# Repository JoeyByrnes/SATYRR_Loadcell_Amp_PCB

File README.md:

# SATYRR Loadcell Amplifier PCB
Loadcell Amplifiers for RoboDesign Lab SATYRR Wheeled-Humanoid robot

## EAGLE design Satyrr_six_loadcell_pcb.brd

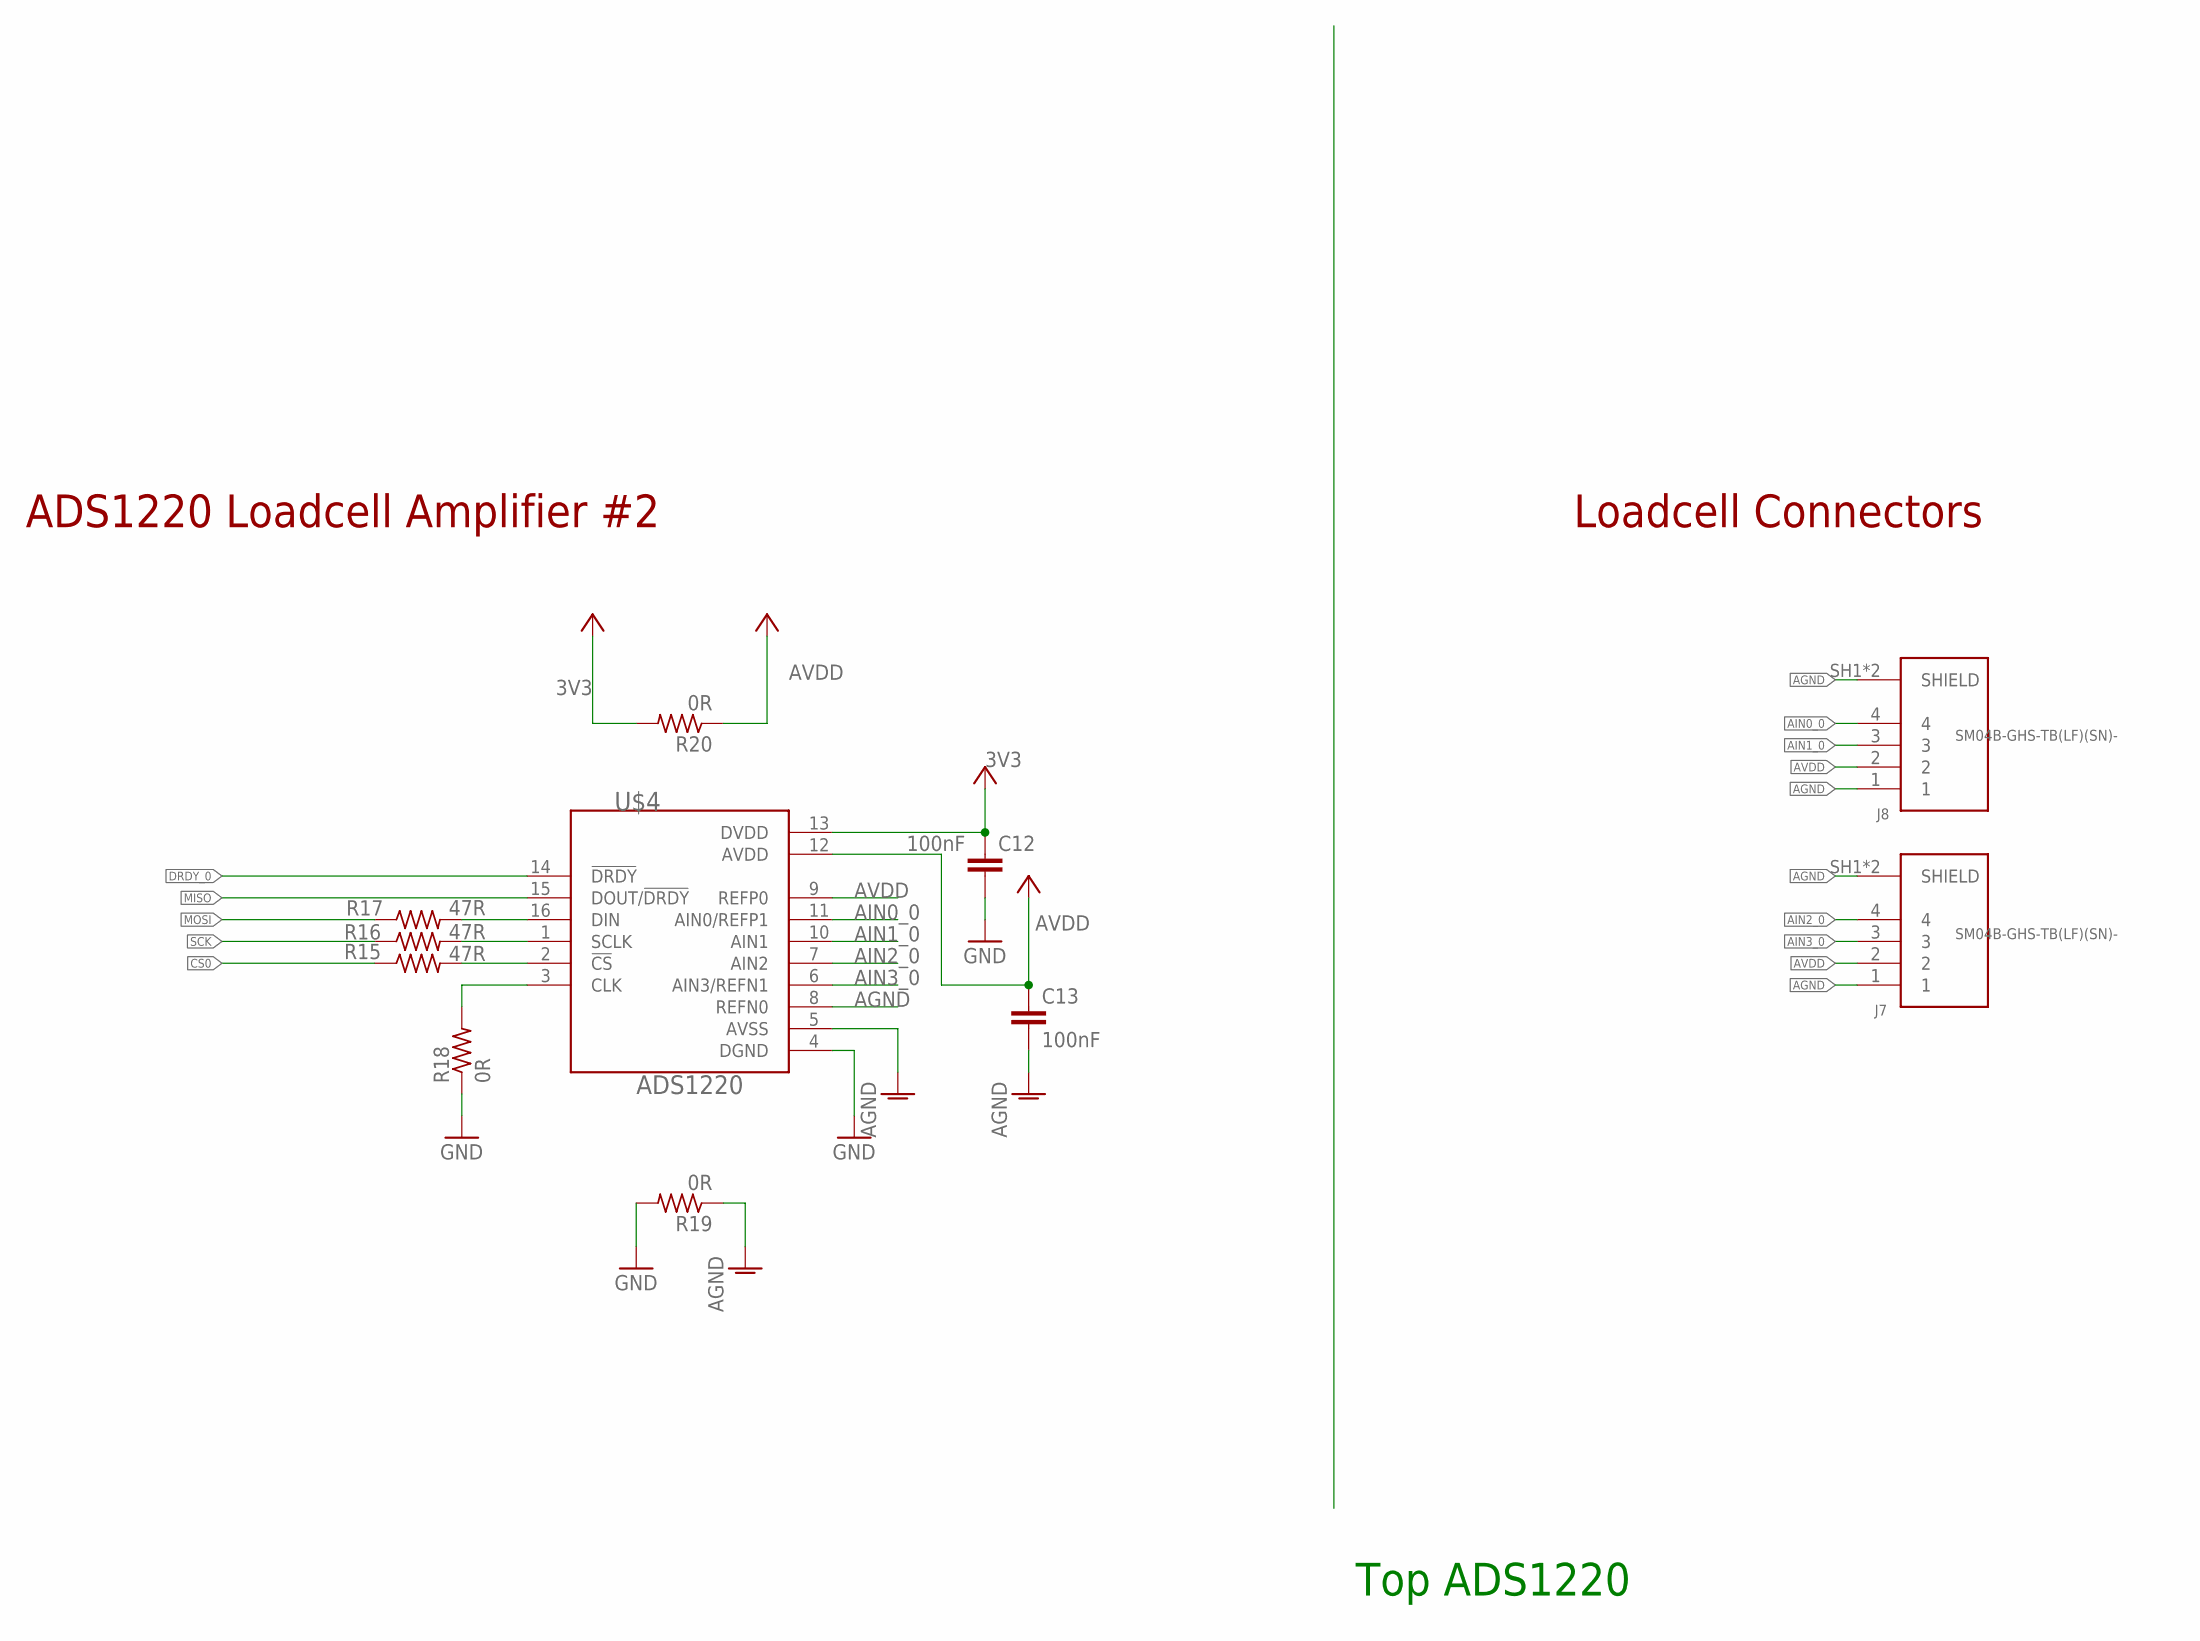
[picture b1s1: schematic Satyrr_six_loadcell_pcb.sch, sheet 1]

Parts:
C12, C13: 100nF; C0603
J7, J8: SM04B-GHS-TB(LF)(SN)-; JST_SM04B-GHS-TB(LF)(SN)-
R15, R16, R17: 47R; R0603
R18, R19, R20: 0R; R0603
U$4: ADS1220; TSSOP-16

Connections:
3V3: C12.1, R20.2, U$4.13 (DVDD); also elsewhere on the board
AGND: C13.2, J7.1, J7.SH1 (SHIELD), J7.SH2 (SHIELD), J8.1, J8.SH1 (SHIELD), J8.SH2 (SHIELD), R19.1, U$4.5 (AVSS), U$4.8 (REFN0); also elsewhere on the board
AIN0_0: J8.4, U$4.11 (AIN0/REFP1)
AIN1_0: J8.3, U$4.10 (AIN1)
AIN2_0: J7.4, U$4.7 (AIN2)
AIN3_0: J7.3, U$4.6 (AIN3/REFN1)
AVDD: C13.1, J7.2, J8.2, R20.1, U$4.9 (REFP0), U$4.12 (AVDD); also elsewhere on the board
CS0: R15.1; also elsewhere on the board
DRDY_0: U$4.14 (!DRDY); also elsewhere on the board
GND: C12.2, R18.1, R19.2, U$4.4 (DGND); also elsewhere on the board
MISO: U$4.15 (DOUT/!DRDY); also elsewhere on the board
MOSI: R17.1; also elsewhere on the board
unnamed: R17.2, U$4.16 (DIN)
unnamed: R16.2, U$4.1 (SCLK)
unnamed: R15.2, U$4.2 (!CS)
unnamed: R18.2, U$4.3 (CLK)
SCK: R16.1; also elsewhere on the board

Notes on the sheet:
Top ADS1220
ADS1220 Loadcell Amplifier #2
Loadcell Connectors

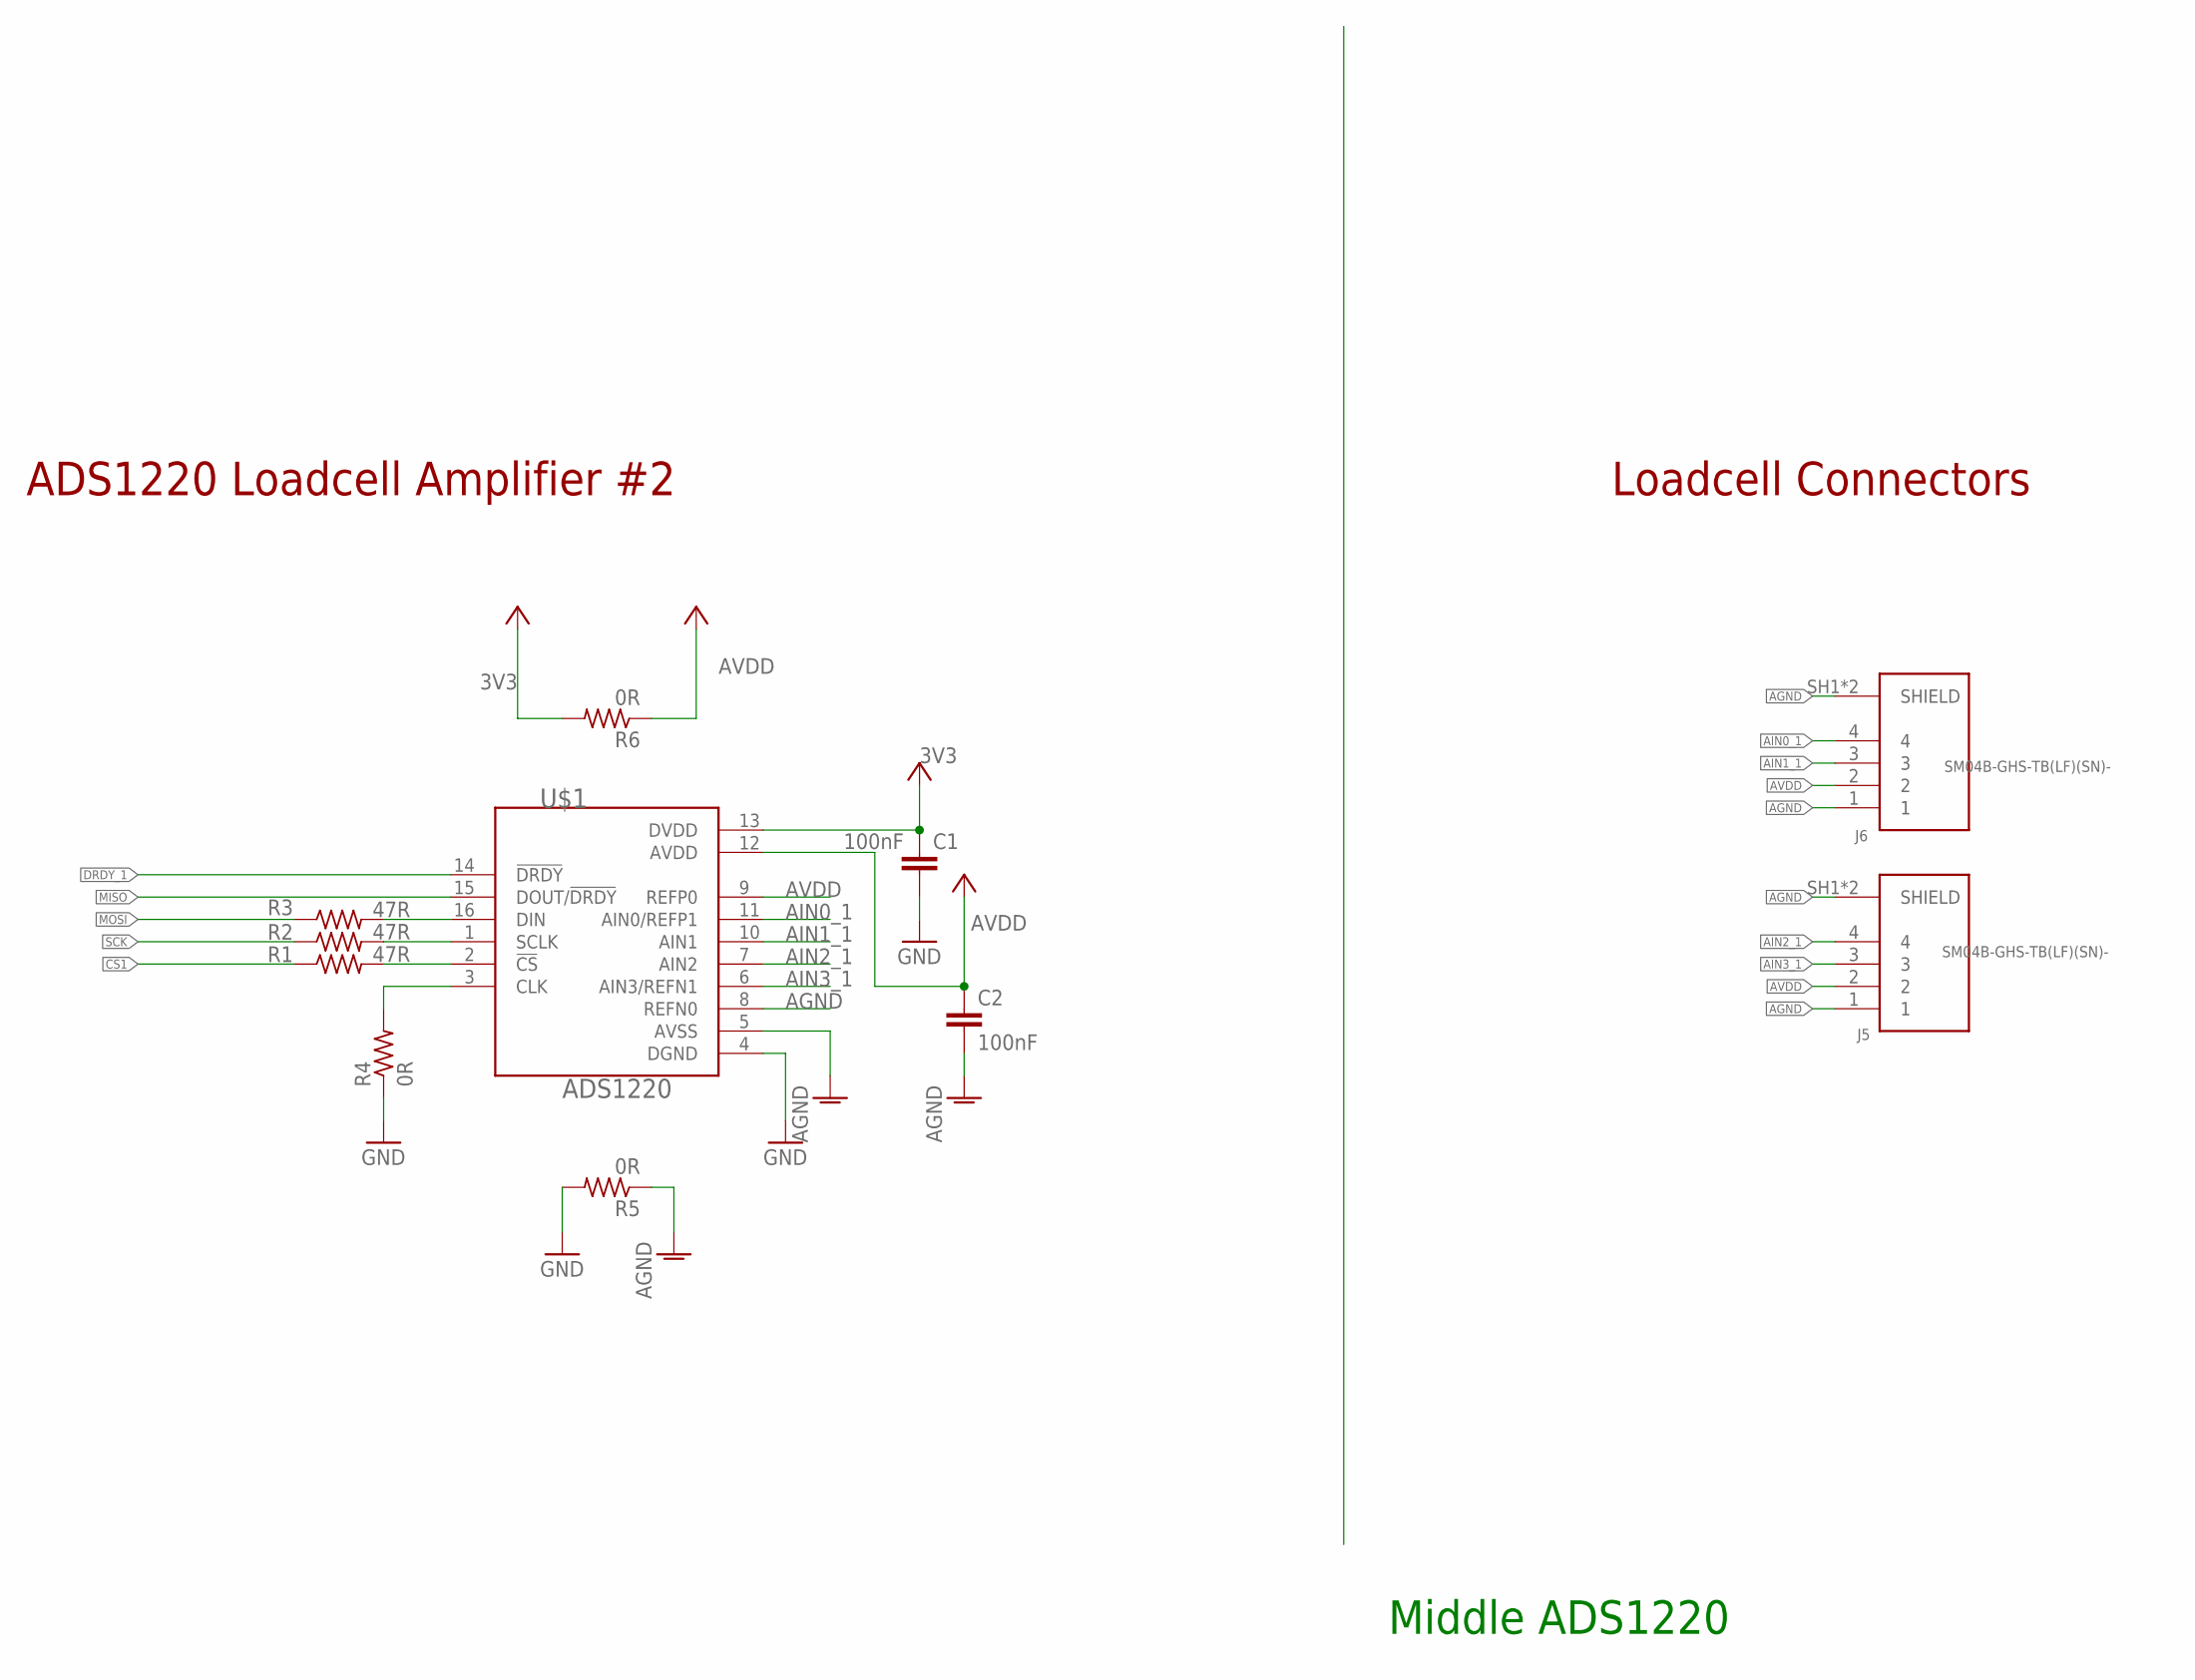
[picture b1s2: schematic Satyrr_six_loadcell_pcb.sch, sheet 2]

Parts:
C1, C2: 100nF; C0603
J5, J6: SM04B-GHS-TB(LF)(SN)-; JST_SM04B-GHS-TB(LF)(SN)-
R1, R2, R3: 47R; R0603
R4, R5, R6: 0R; R0603
U$1: ADS1220; TSSOP-16

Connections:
3V3: C1.1, R6.2, U$1.13 (DVDD); also elsewhere on the board
AGND: C2.2, J5.1, J5.SH1 (SHIELD), J5.SH2 (SHIELD), J6.1, J6.SH1 (SHIELD), J6.SH2 (SHIELD), R5.1, U$1.5 (AVSS), U$1.8 (REFN0); also elsewhere on the board
AIN0_1: J6.4, U$1.11 (AIN0/REFP1)
AIN1_1: J6.3, U$1.10 (AIN1)
AIN2_1: J5.4, U$1.7 (AIN2)
AIN3_1: J5.3, U$1.6 (AIN3/REFN1)
AVDD: C2.1, J5.2, J6.2, R6.1, U$1.9 (REFP0), U$1.12 (AVDD); also elsewhere on the board
CS1: R1.1; also elsewhere on the board
DRDY_1: U$1.14 (!DRDY); also elsewhere on the board
GND: C1.2, R4.1, R5.2, U$1.4 (DGND); also elsewhere on the board
MISO: U$1.15 (DOUT/!DRDY); also elsewhere on the board
MOSI: R3.1; also elsewhere on the board
unnamed: R3.2, U$1.16 (DIN)
unnamed: R2.2, U$1.1 (SCLK)
unnamed: R1.2, U$1.2 (!CS)
unnamed: R4.2, U$1.3 (CLK)
SCK: R2.1; also elsewhere on the board

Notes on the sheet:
Middle ADS1220
ADS1220 Loadcell Amplifier #2
Loadcell Connectors

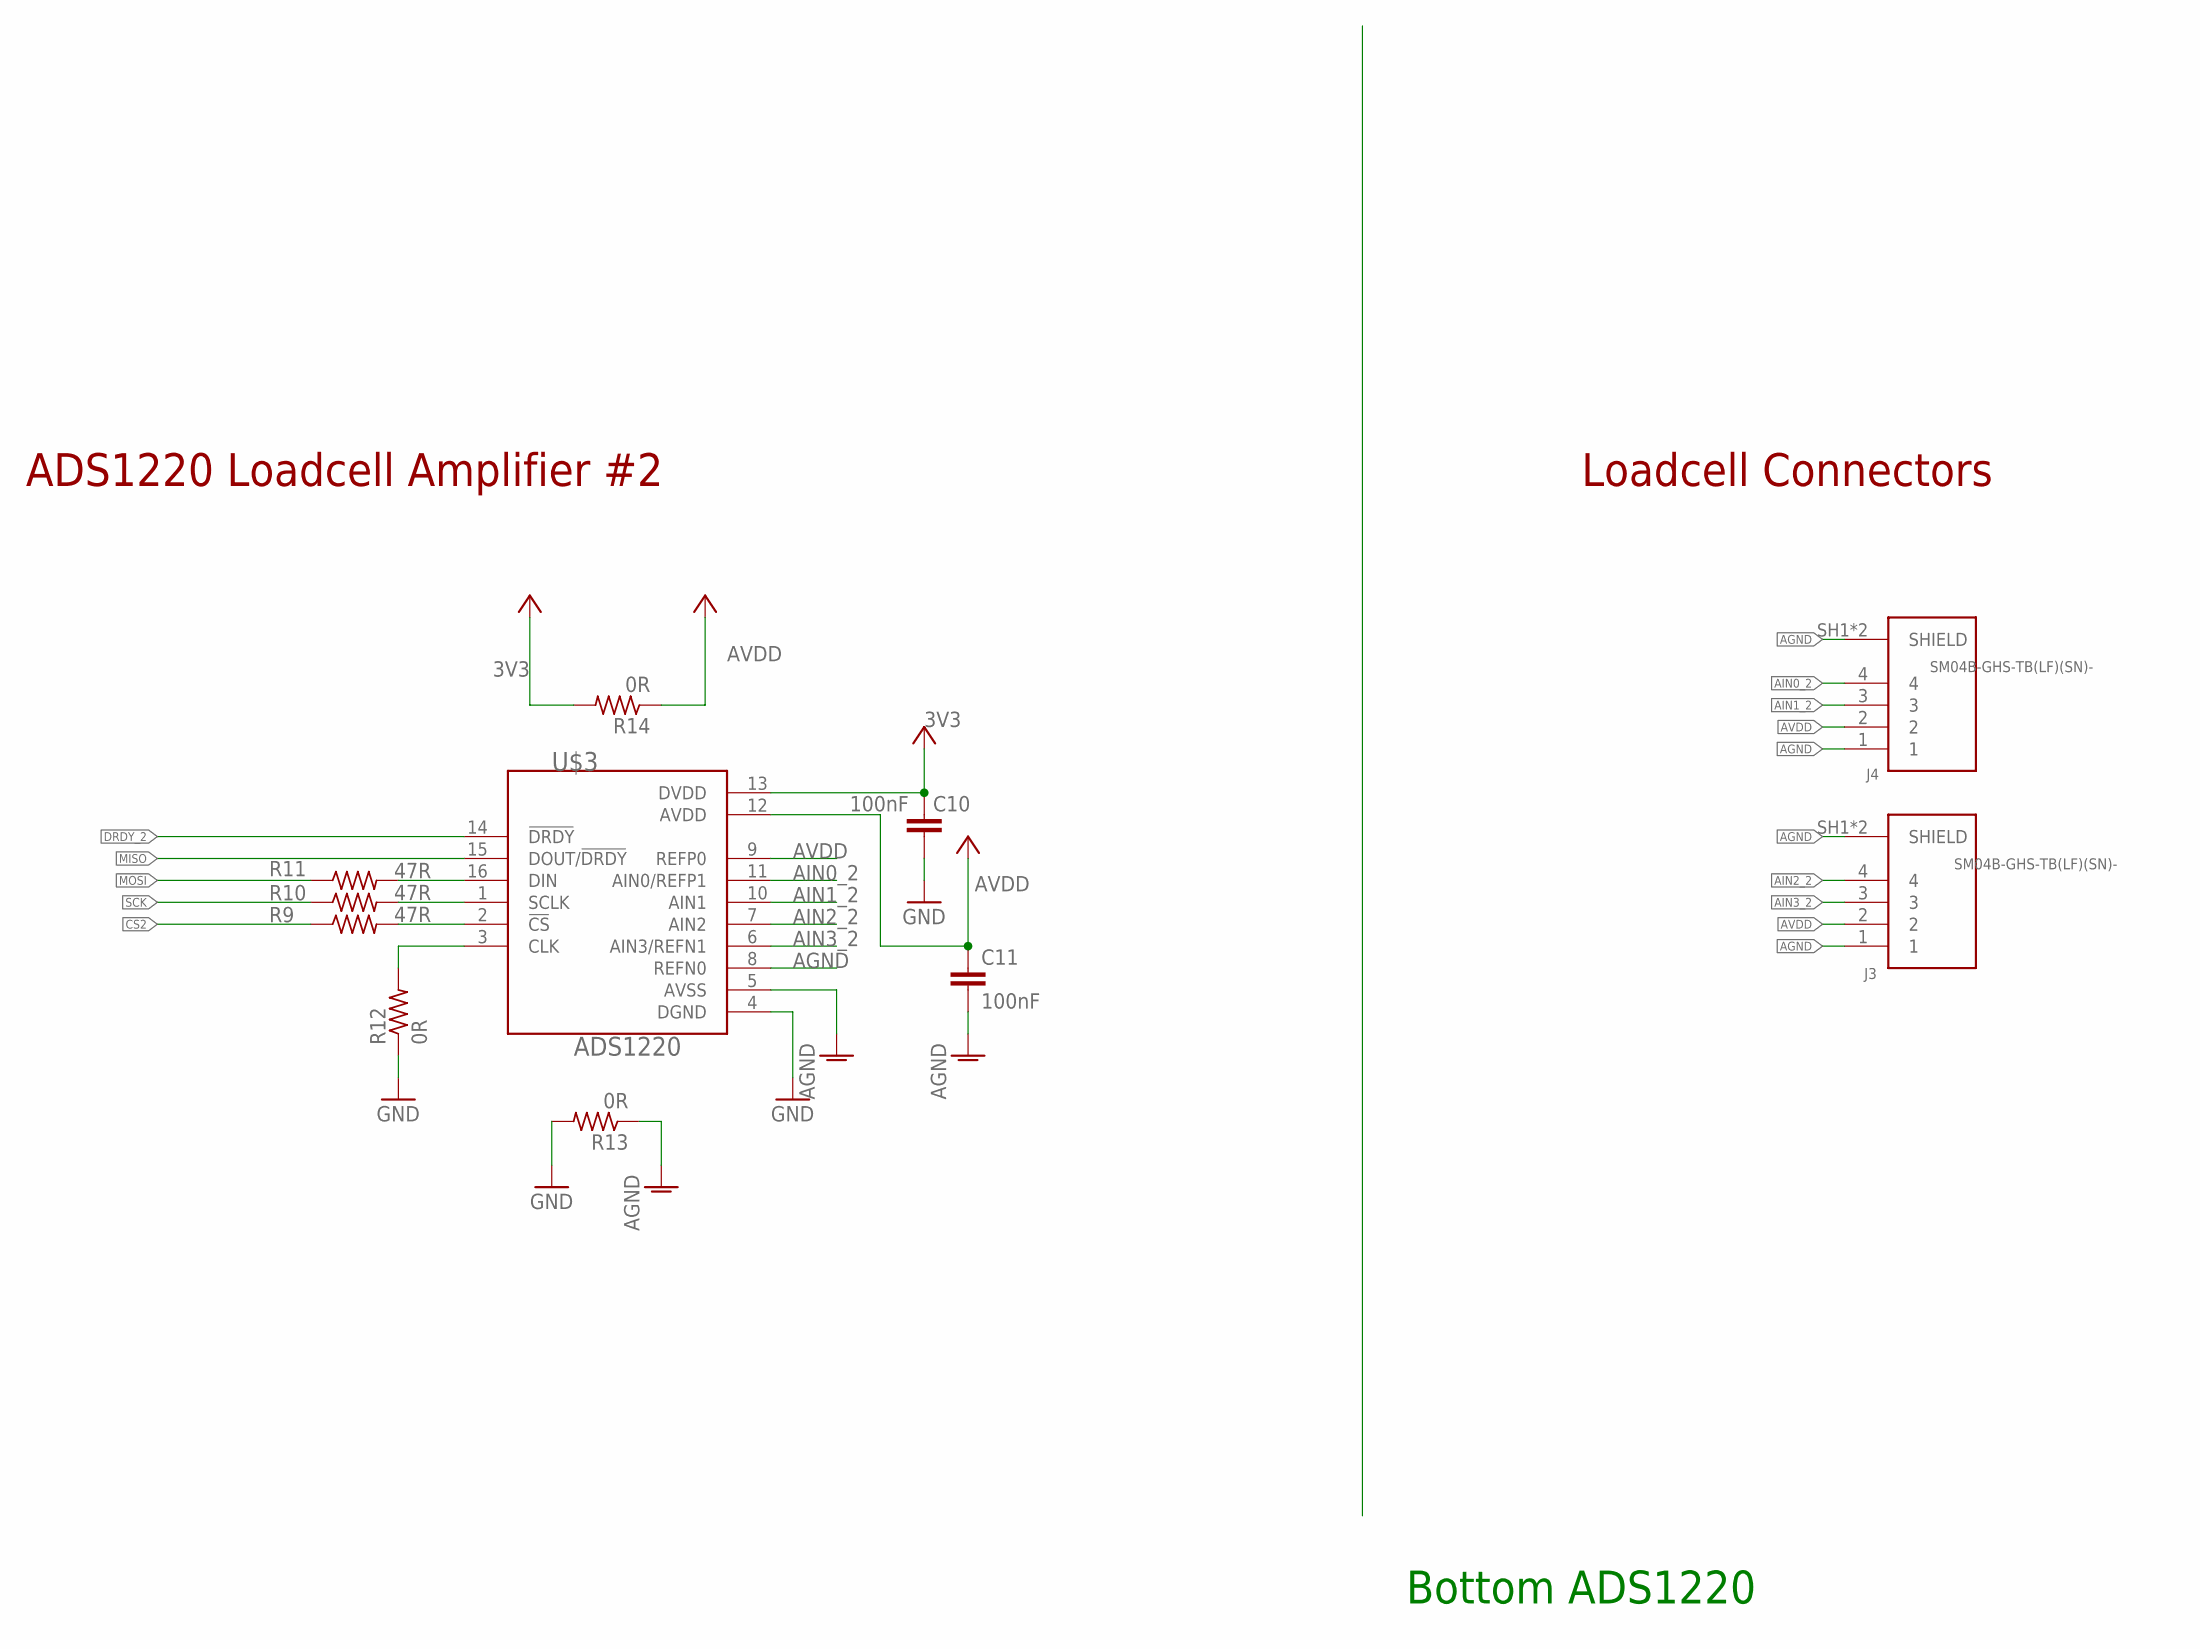
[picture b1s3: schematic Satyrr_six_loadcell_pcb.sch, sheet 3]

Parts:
C10, C11: 100nF; C0603
J3, J4: SM04B-GHS-TB(LF)(SN)-; JST_SM04B-GHS-TB(LF)(SN)-
R9, R10, R11: 47R; R0603
R12, R13, R14: 0R; R0603
U$3: ADS1220; TSSOP-16

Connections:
3V3: C10.1, R14.2, U$3.13 (DVDD); also elsewhere on the board
AGND: C11.2, J3.1, J3.SH1 (SHIELD), J3.SH2 (SHIELD), J4.1, J4.SH1 (SHIELD), J4.SH2 (SHIELD), R13.1, U$3.5 (AVSS), U$3.8 (REFN0); also elsewhere on the board
AIN0_2: J4.4, U$3.11 (AIN0/REFP1)
AIN1_2: J4.3, U$3.10 (AIN1)
AIN2_2: J3.4, U$3.7 (AIN2)
AIN3_2: J3.3, U$3.6 (AIN3/REFN1)
AVDD: C11.1, J3.2, J4.2, R14.1, U$3.9 (REFP0), U$3.12 (AVDD); also elsewhere on the board
CS2: R9.1; also elsewhere on the board
DRDY_2: U$3.14 (!DRDY); also elsewhere on the board
GND: C10.2, R12.1, R13.2, U$3.4 (DGND); also elsewhere on the board
MISO: U$3.15 (DOUT/!DRDY); also elsewhere on the board
MOSI: R11.1; also elsewhere on the board
unnamed: R11.2, U$3.16 (DIN)
unnamed: R10.2, U$3.1 (SCLK)
unnamed: R9.2, U$3.2 (!CS)
unnamed: R12.2, U$3.3 (CLK)
SCK: R10.1; also elsewhere on the board

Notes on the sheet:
Bottom ADS1220
ADS1220 Loadcell Amplifier #2
Loadcell Connectors

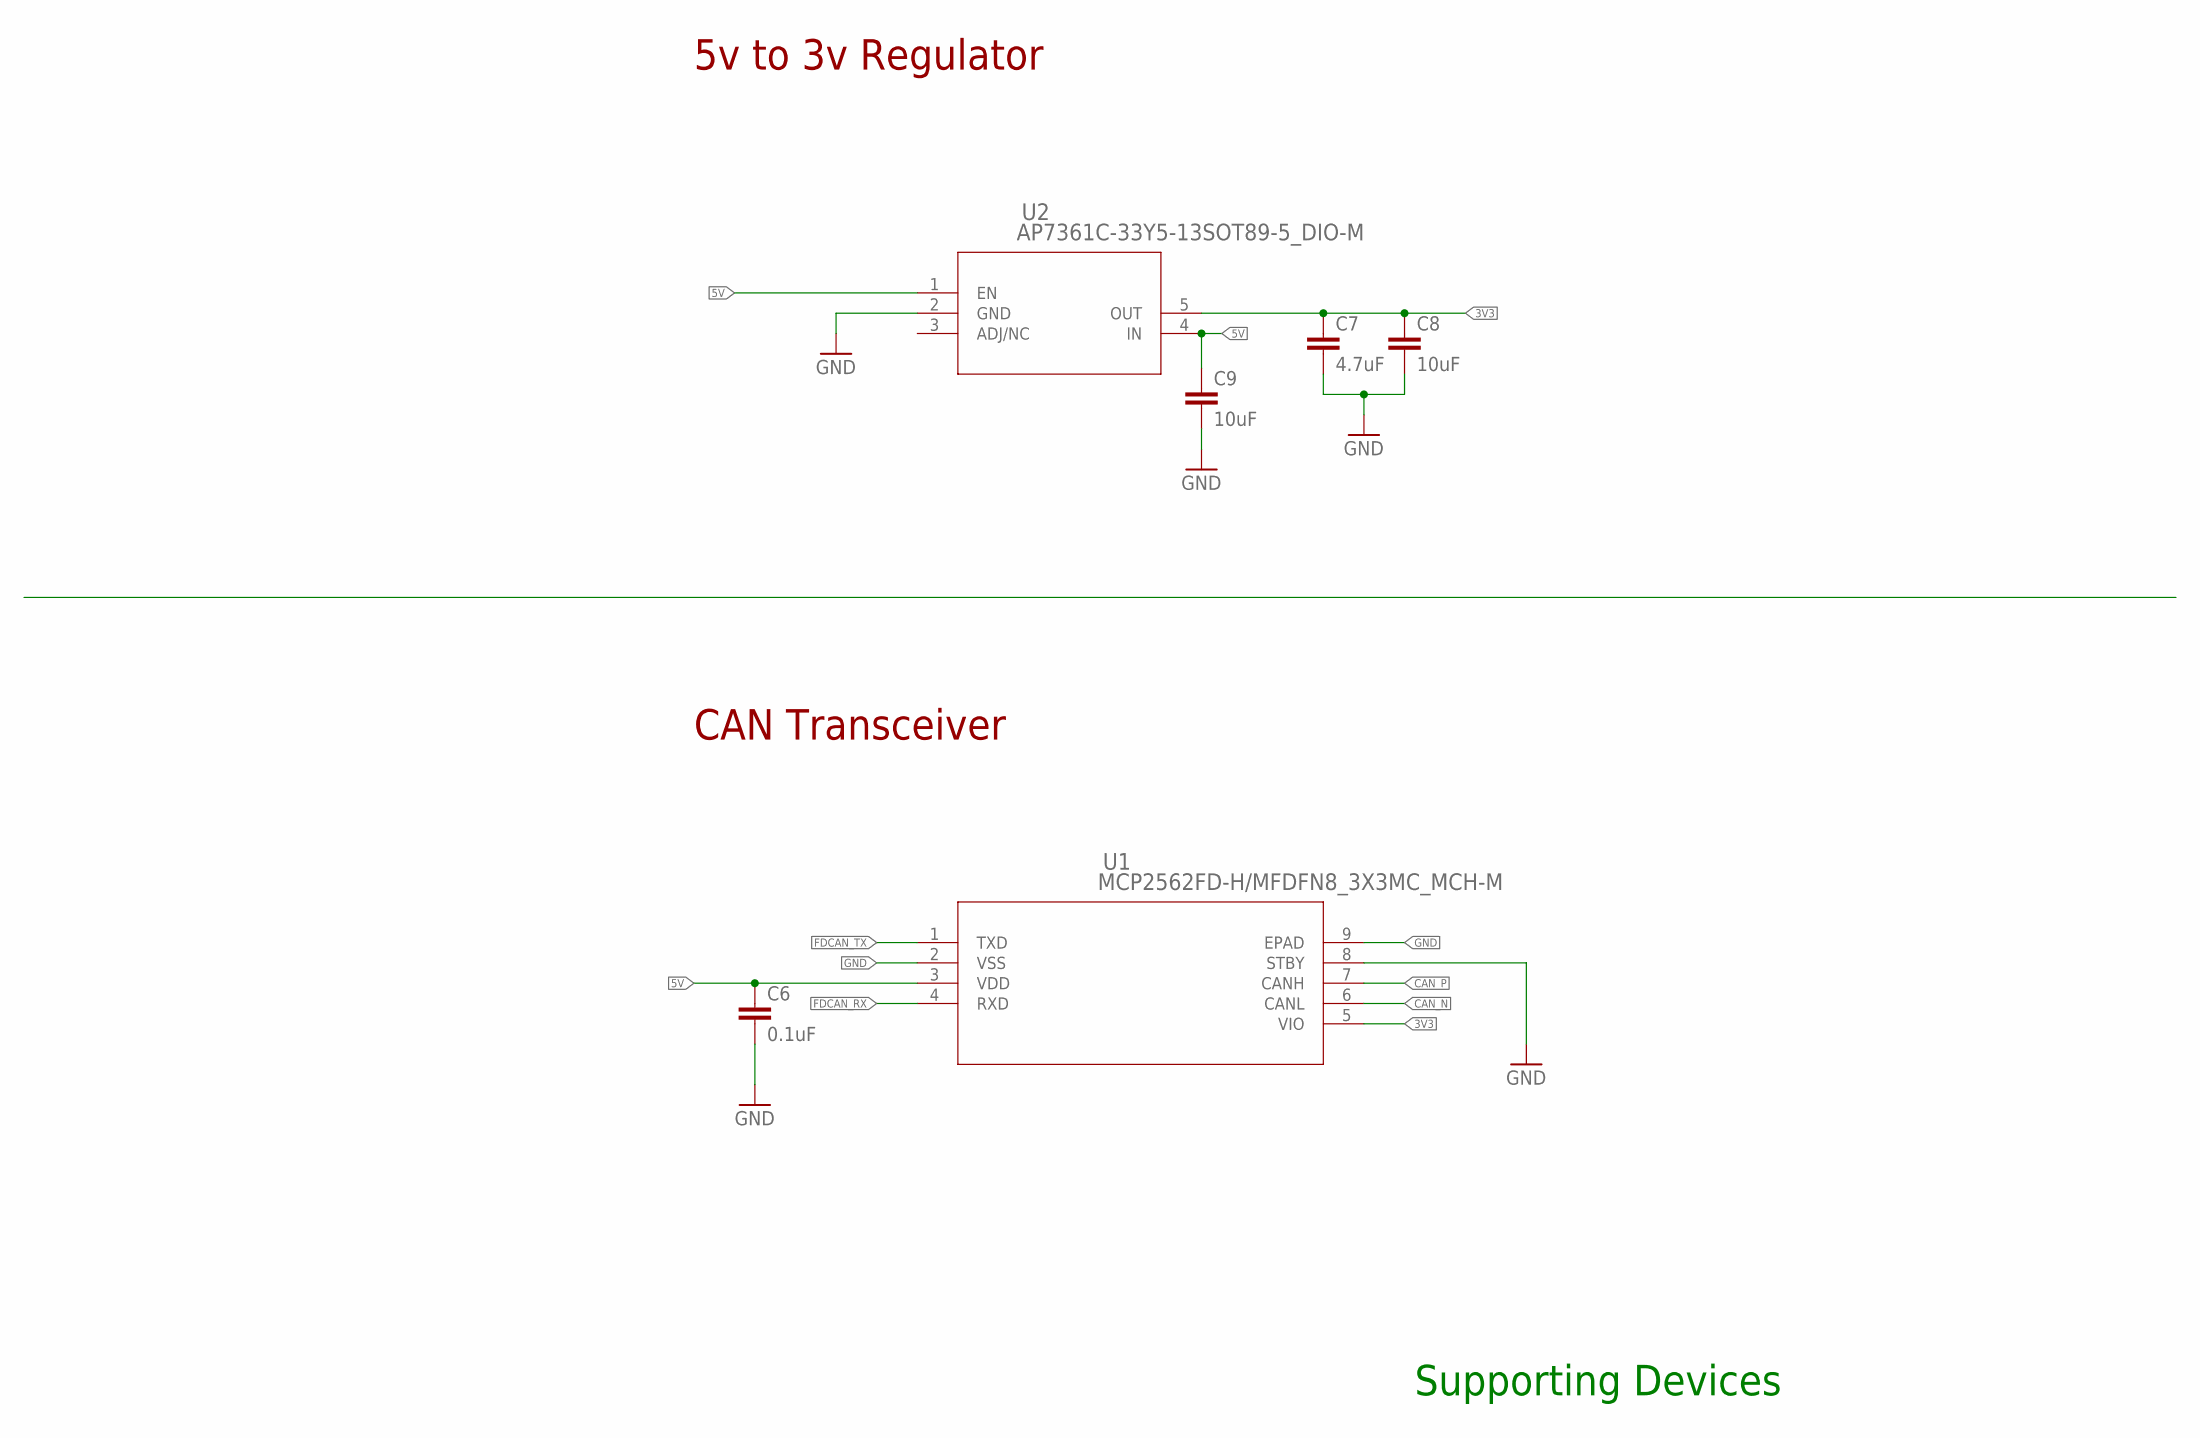
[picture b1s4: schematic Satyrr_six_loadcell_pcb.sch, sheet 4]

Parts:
C6: 0.1uF; C0603
C7: 4.7uF; C0603
C8, C9: 10uF; C0603
U1: MCP2562FD-H/MFDFN8_3X3MC_MCH-M; DFN8_3X3MC_MCH-M
U2: AP7361C-33Y5-13SOT89-5_DIO-M; SOT89-5_DIO-M

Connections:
3V3: C7.1, C8.1, U1.5 (VIO), U2.5 (OUT); also elsewhere on the board
5V: C6.1, C9.1, U1.3 (VDD), U2.1 (EN), U2.4 (IN); also elsewhere on the board
CAN_N: U1.6 (CANL); also elsewhere on the board
CAN_P: U1.7 (CANH); also elsewhere on the board
FDCAN_RX: U1.4 (RXD); also elsewhere on the board
FDCAN_TX: U1.1 (TXD); also elsewhere on the board
GND: C6.2, C7.2, C8.2, C9.2, U1.2 (VSS), U1.8 (STBY), U1.9 (EPAD), U2.2 (GND); also elsewhere on the board

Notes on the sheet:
5v to 3v Regulator
CAN Transceiver
Supporting Devices

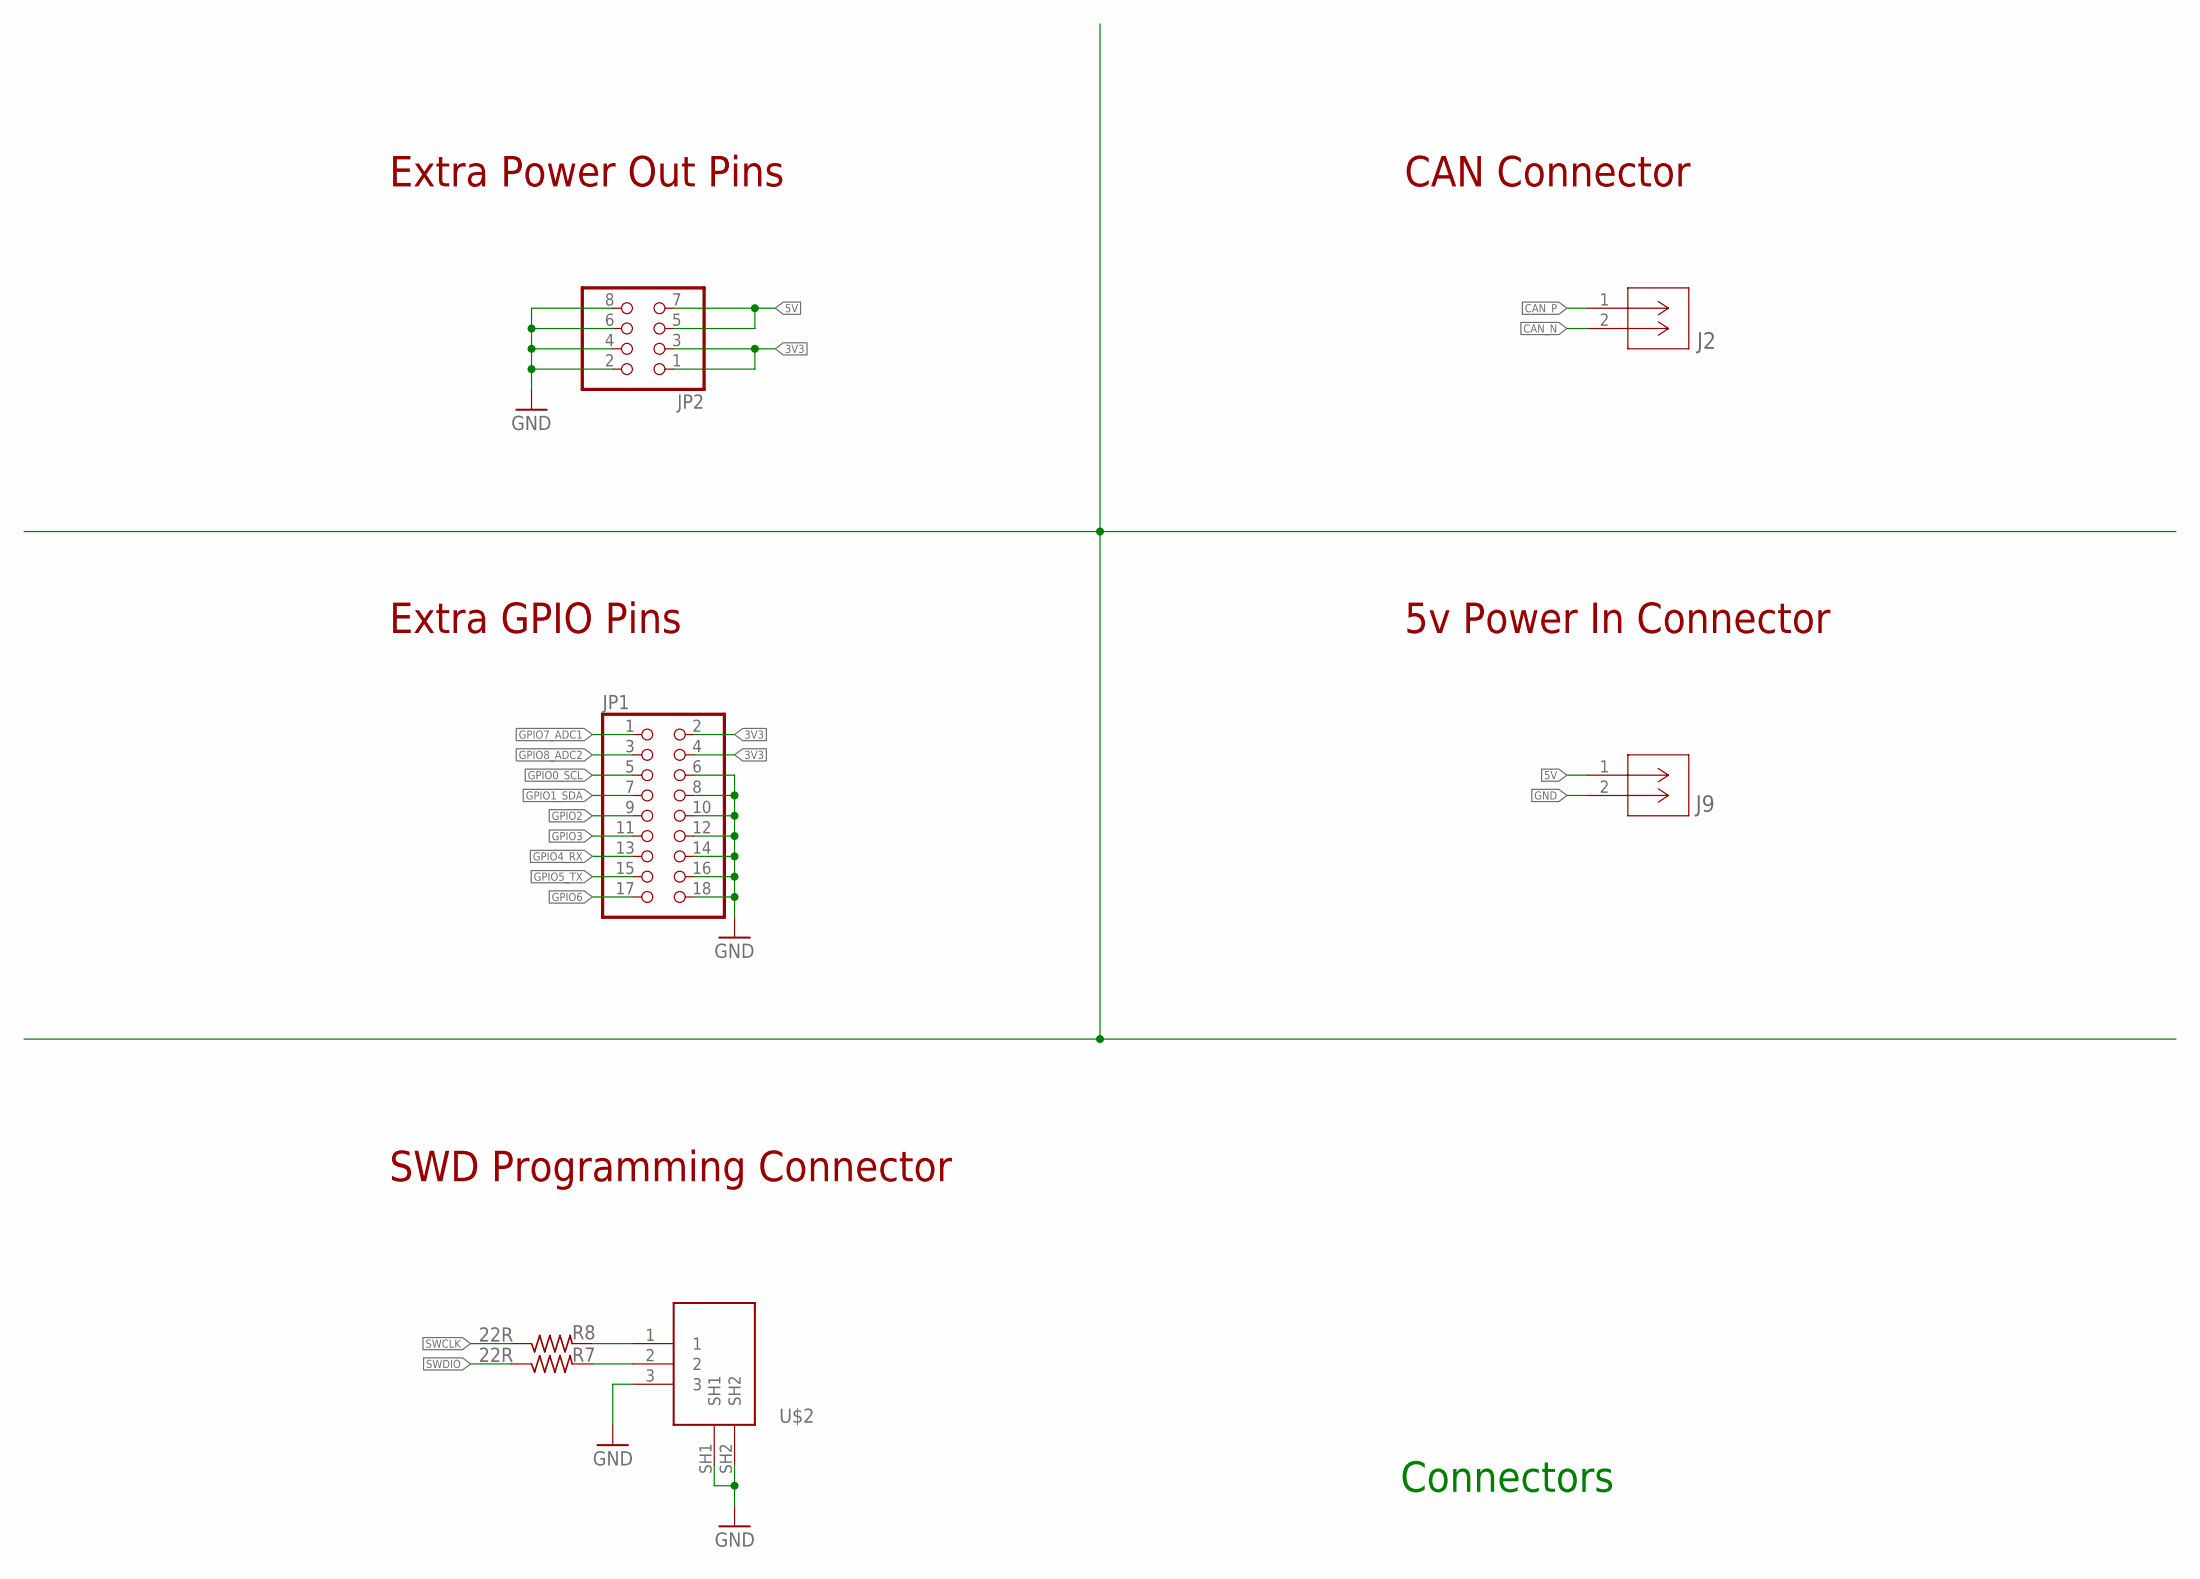
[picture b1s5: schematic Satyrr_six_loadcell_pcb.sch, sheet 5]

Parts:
J2: SM02BGHSTBLFSN; CONN_SM02BGHSTB_JST
J9: 22057025; CON_22057025_MOL
JP1: PINHD-2X9; 2X09
JP2: PINHD-2X4; 2X04
R7, R8: 22R; R0603
U$2: 125SH-G-03-TR-SMT

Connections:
3V3: JP1.2, JP1.4, JP2.1, JP2.3; also elsewhere on the board
5V: J9.1, JP2.5, JP2.7; also elsewhere on the board
CAN_N: J2.2; also elsewhere on the board
CAN_P: J2.1; also elsewhere on the board
GND: J9.2, JP1.6, JP1.8, JP1.10, JP1.12, JP1.14, JP1.16, JP1.18, JP2.2, JP2.4, JP2.6, JP2.8, U$2.3, U$2.SH1, U$2.SH2; also elsewhere on the board
GPIO0_SCL: JP1.5; also elsewhere on the board
GPIO1_SDA: JP1.7; also elsewhere on the board
GPIO2: JP1.9; also elsewhere on the board
GPIO3: JP1.11; also elsewhere on the board
GPIO4_RX: JP1.13; also elsewhere on the board
GPIO5_TX: JP1.15; also elsewhere on the board
GPIO6: JP1.17; also elsewhere on the board
GPIO7_ADC1: JP1.1; also elsewhere on the board
GPIO8_ADC2: JP1.3; also elsewhere on the board
SWCLK: R8.1; also elsewhere on the board
SWCLK_C: R8.2, U$2.1
SWDIO: R7.1; also elsewhere on the board
SWDIO_C: R7.2, U$2.2

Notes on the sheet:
U$2
Extra Power Out Pins
Extra GPIO Pins
CAN Connector
5v Power In Connector
SWD Programming Connector
Connectors

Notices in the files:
parts and their libraries:
COPYRIGHT: Copyright (C) 2023 Ultra Librarian. All rights reserved.
COPYRIGHT: Copyright (C) 2022 Ultra Librarian. All rights reserved.
